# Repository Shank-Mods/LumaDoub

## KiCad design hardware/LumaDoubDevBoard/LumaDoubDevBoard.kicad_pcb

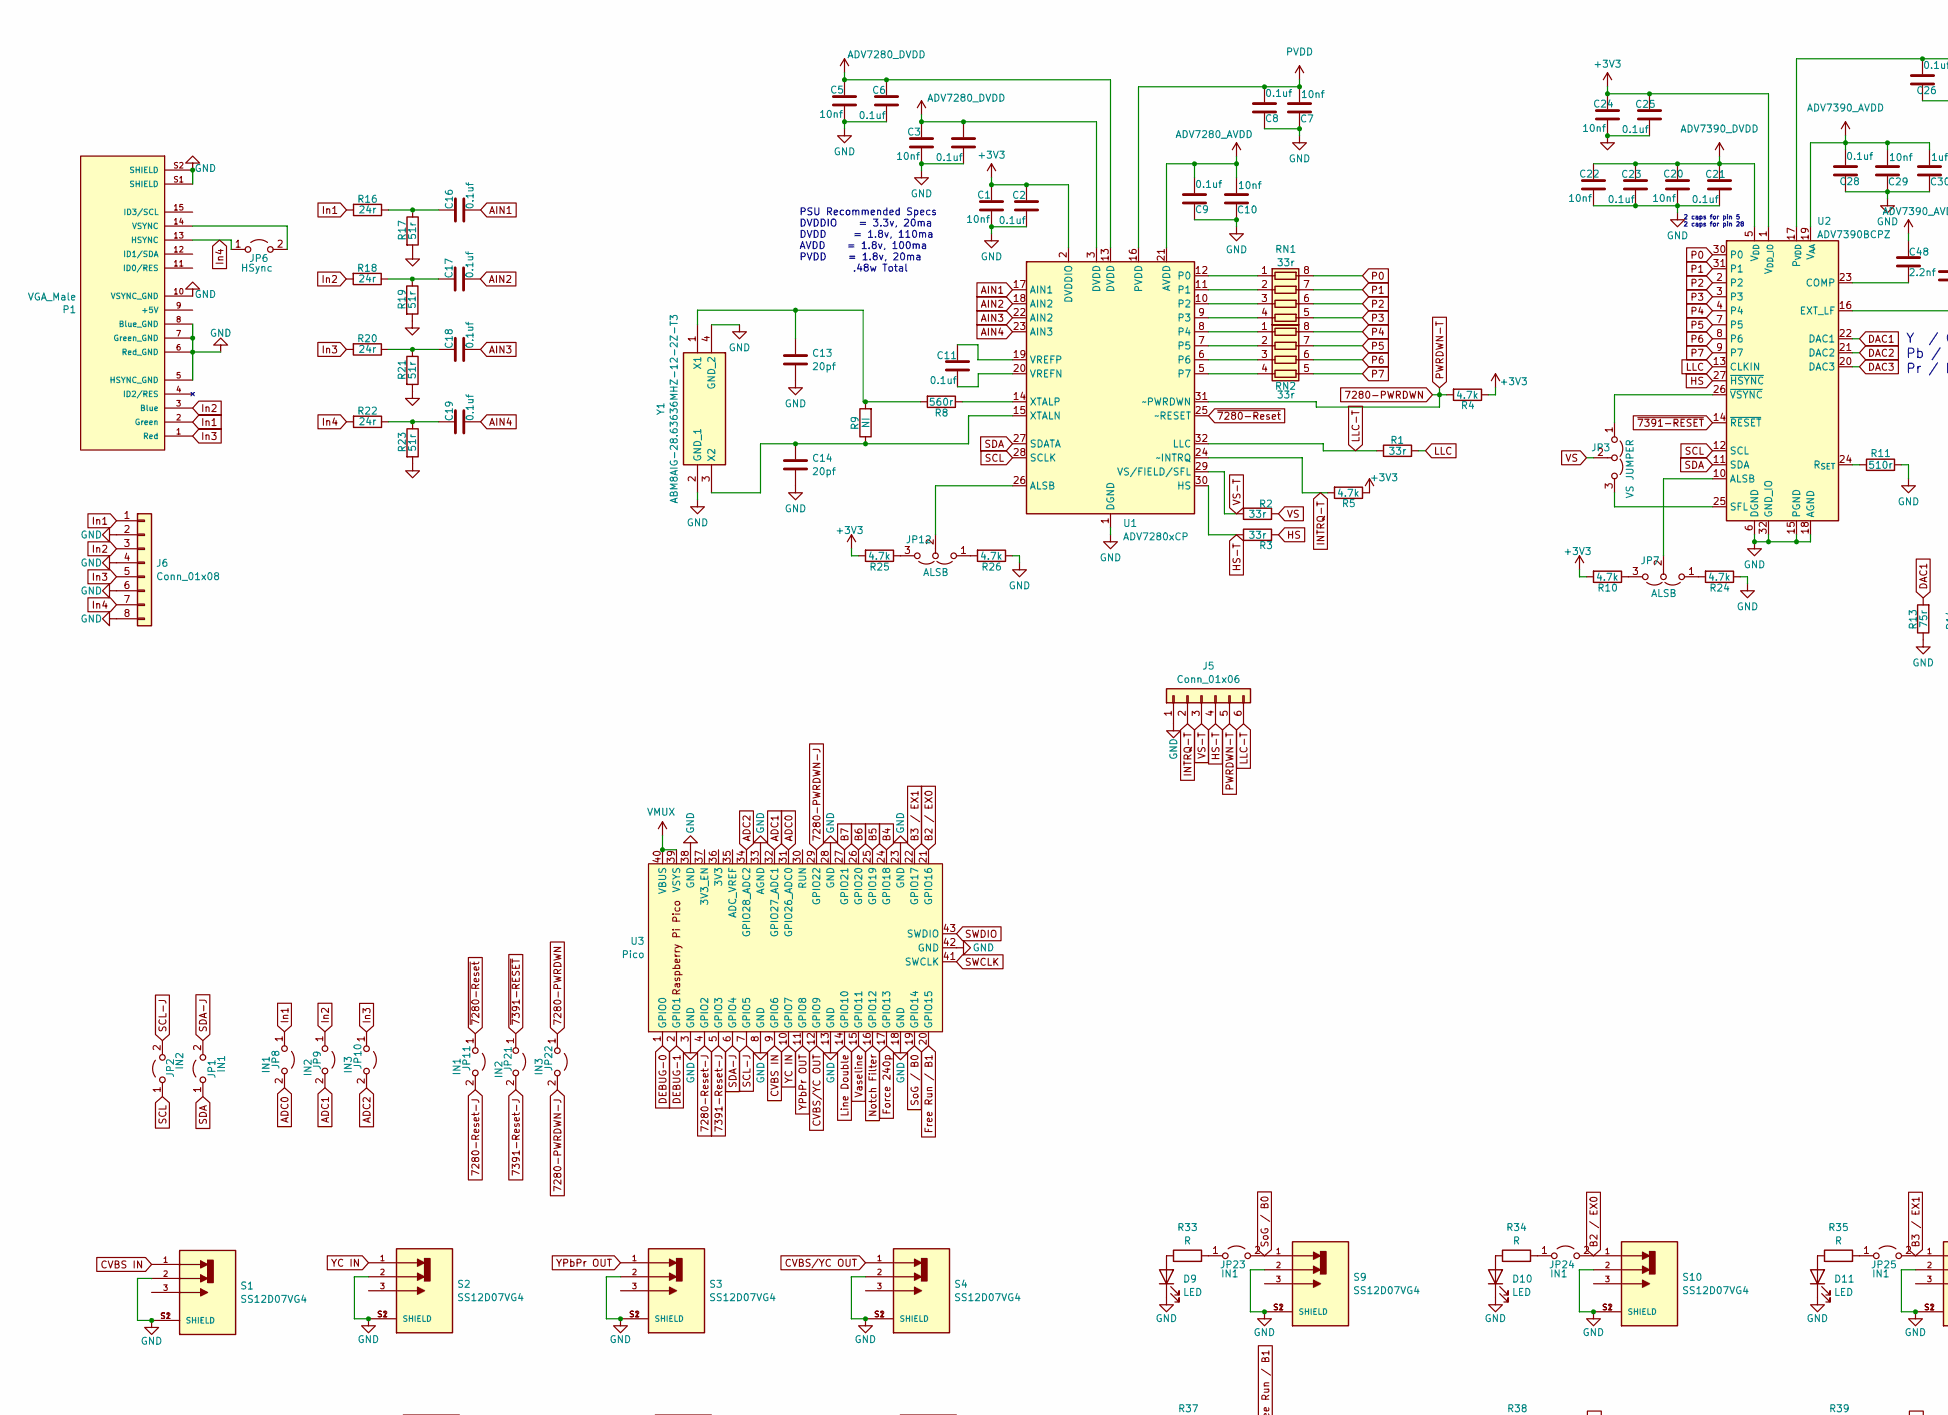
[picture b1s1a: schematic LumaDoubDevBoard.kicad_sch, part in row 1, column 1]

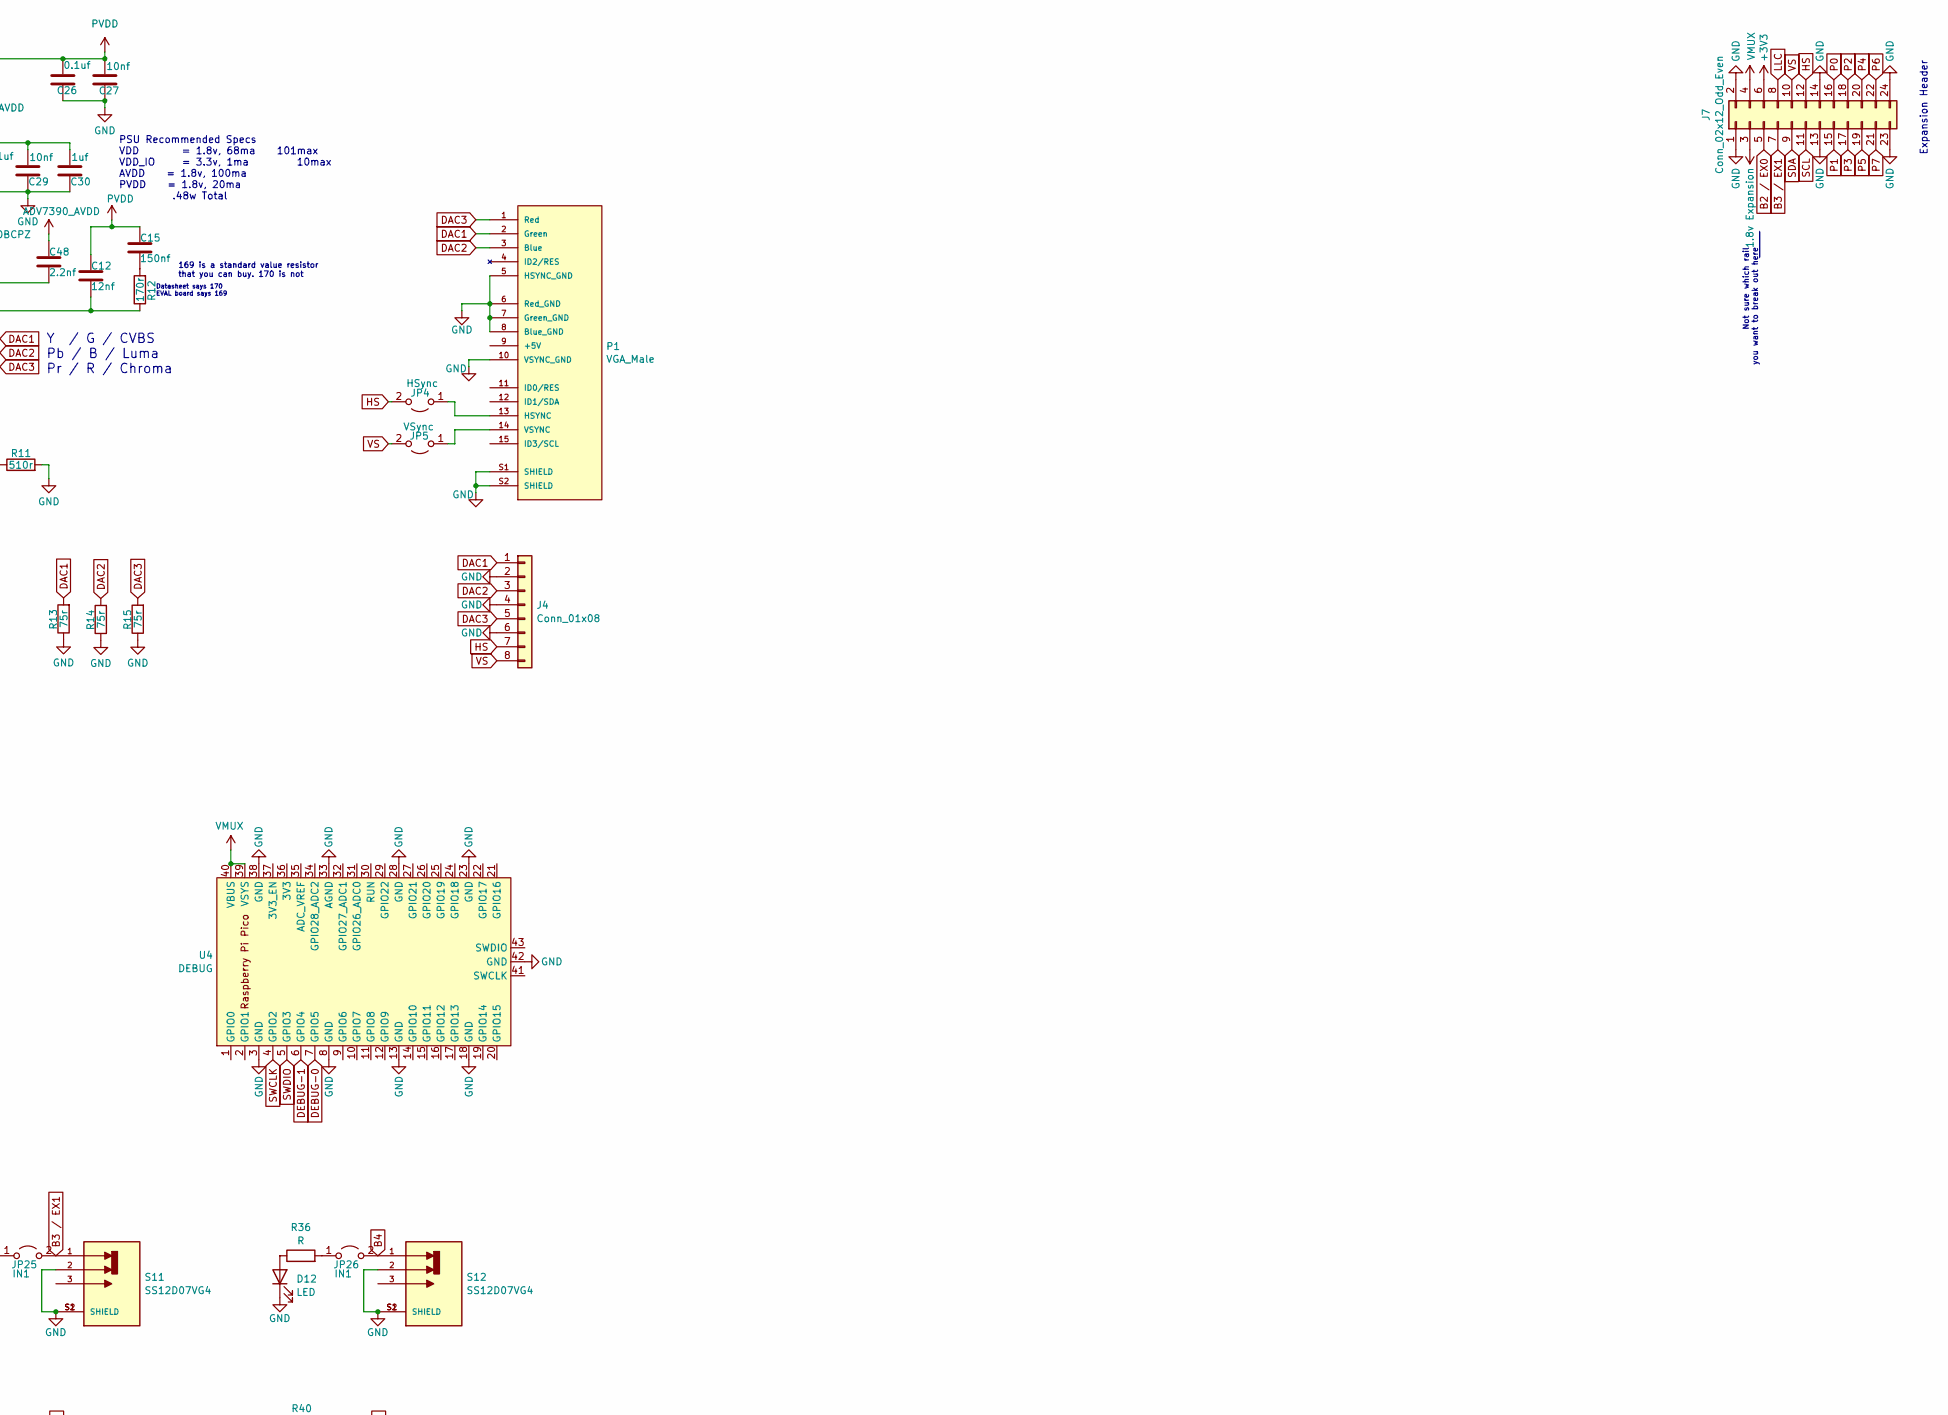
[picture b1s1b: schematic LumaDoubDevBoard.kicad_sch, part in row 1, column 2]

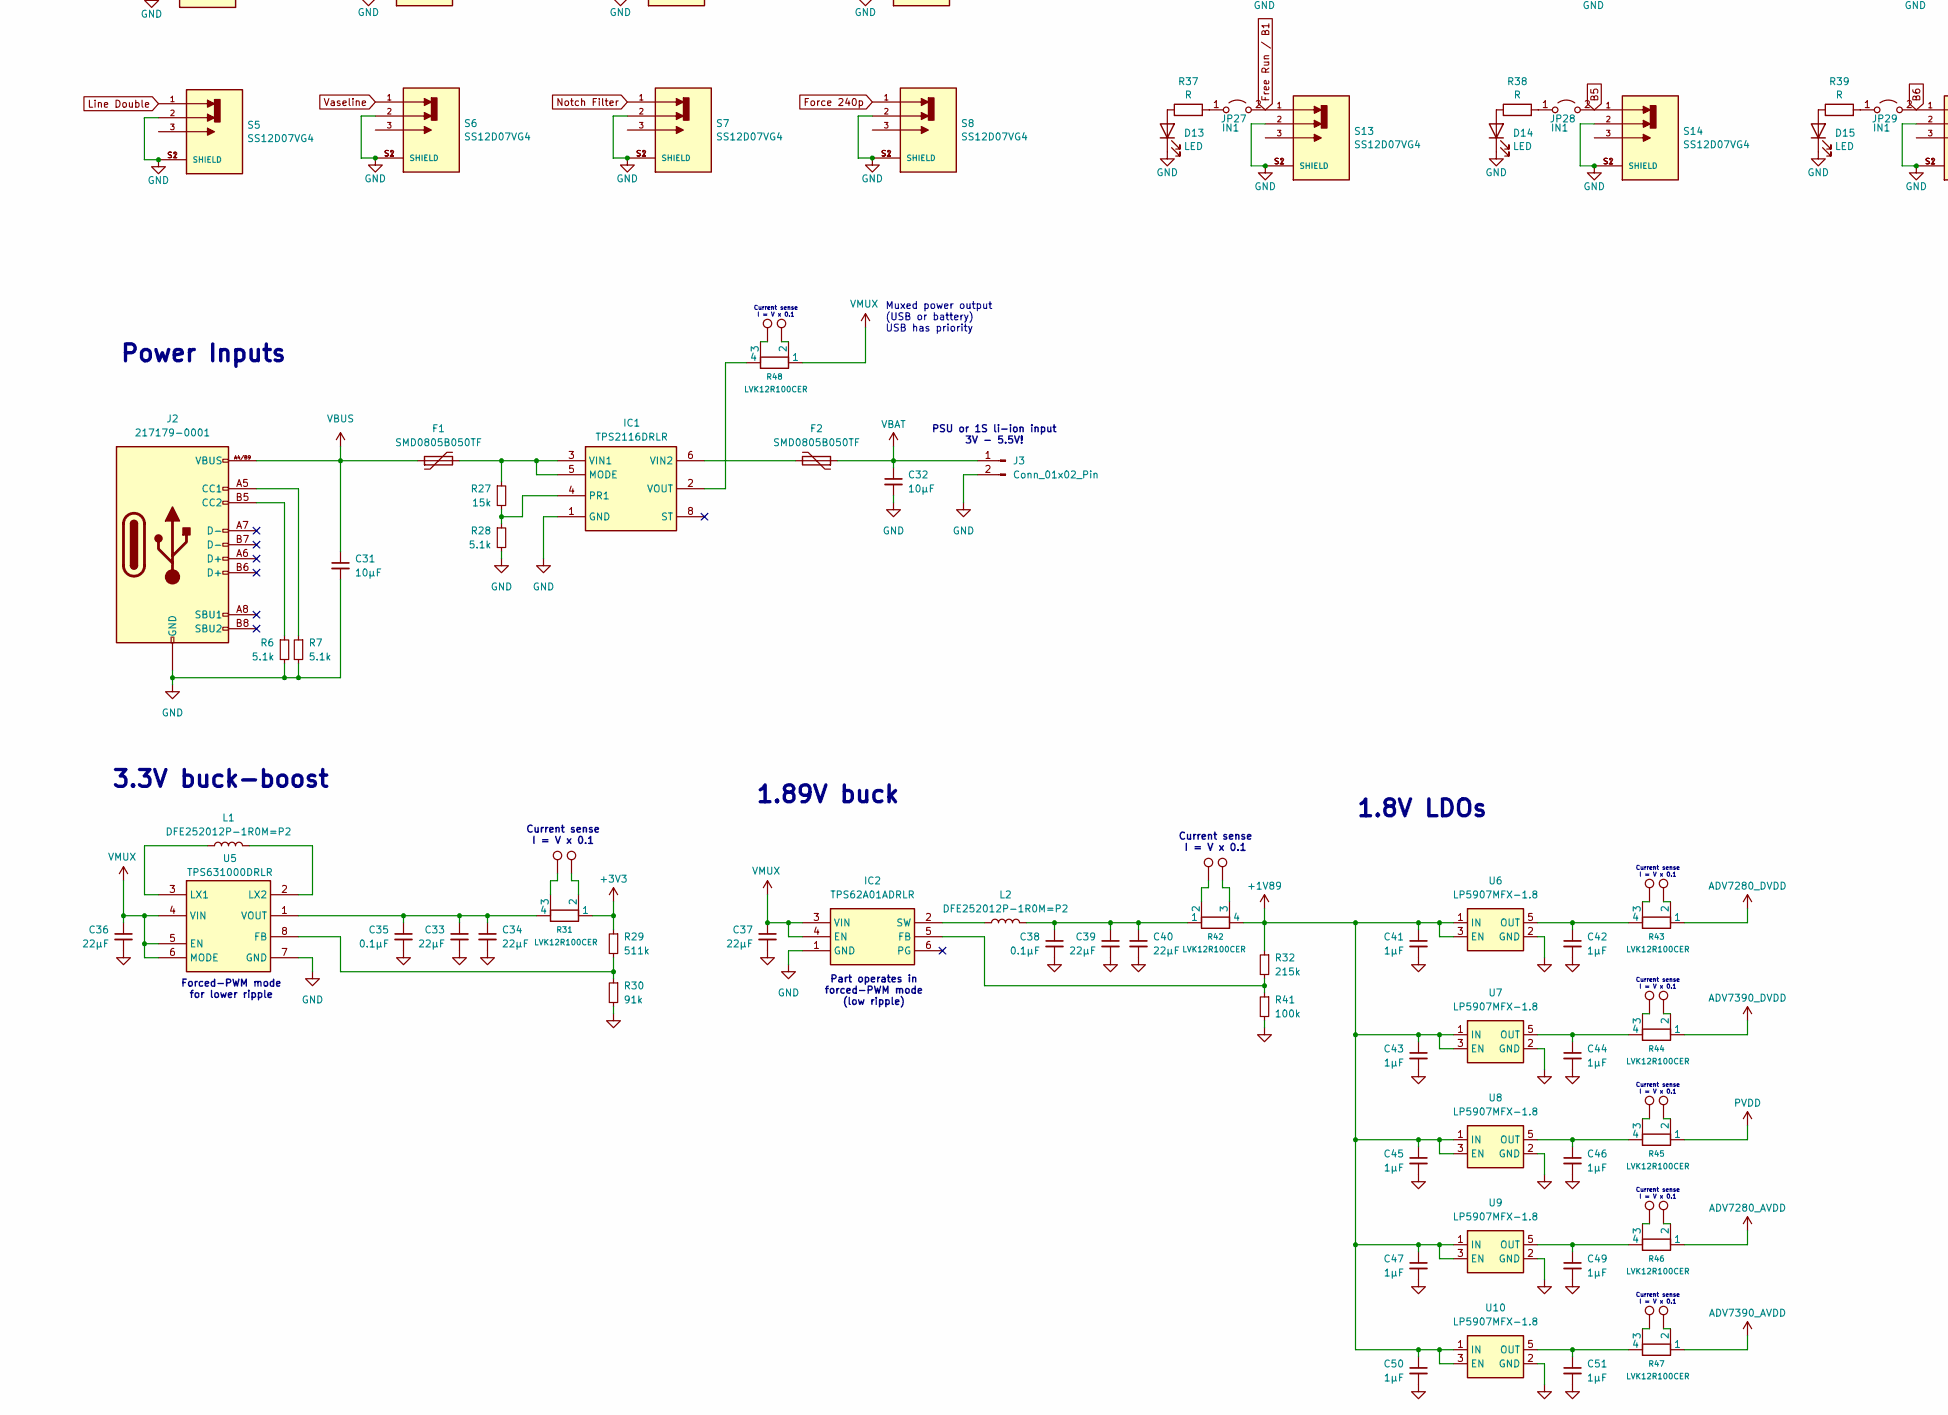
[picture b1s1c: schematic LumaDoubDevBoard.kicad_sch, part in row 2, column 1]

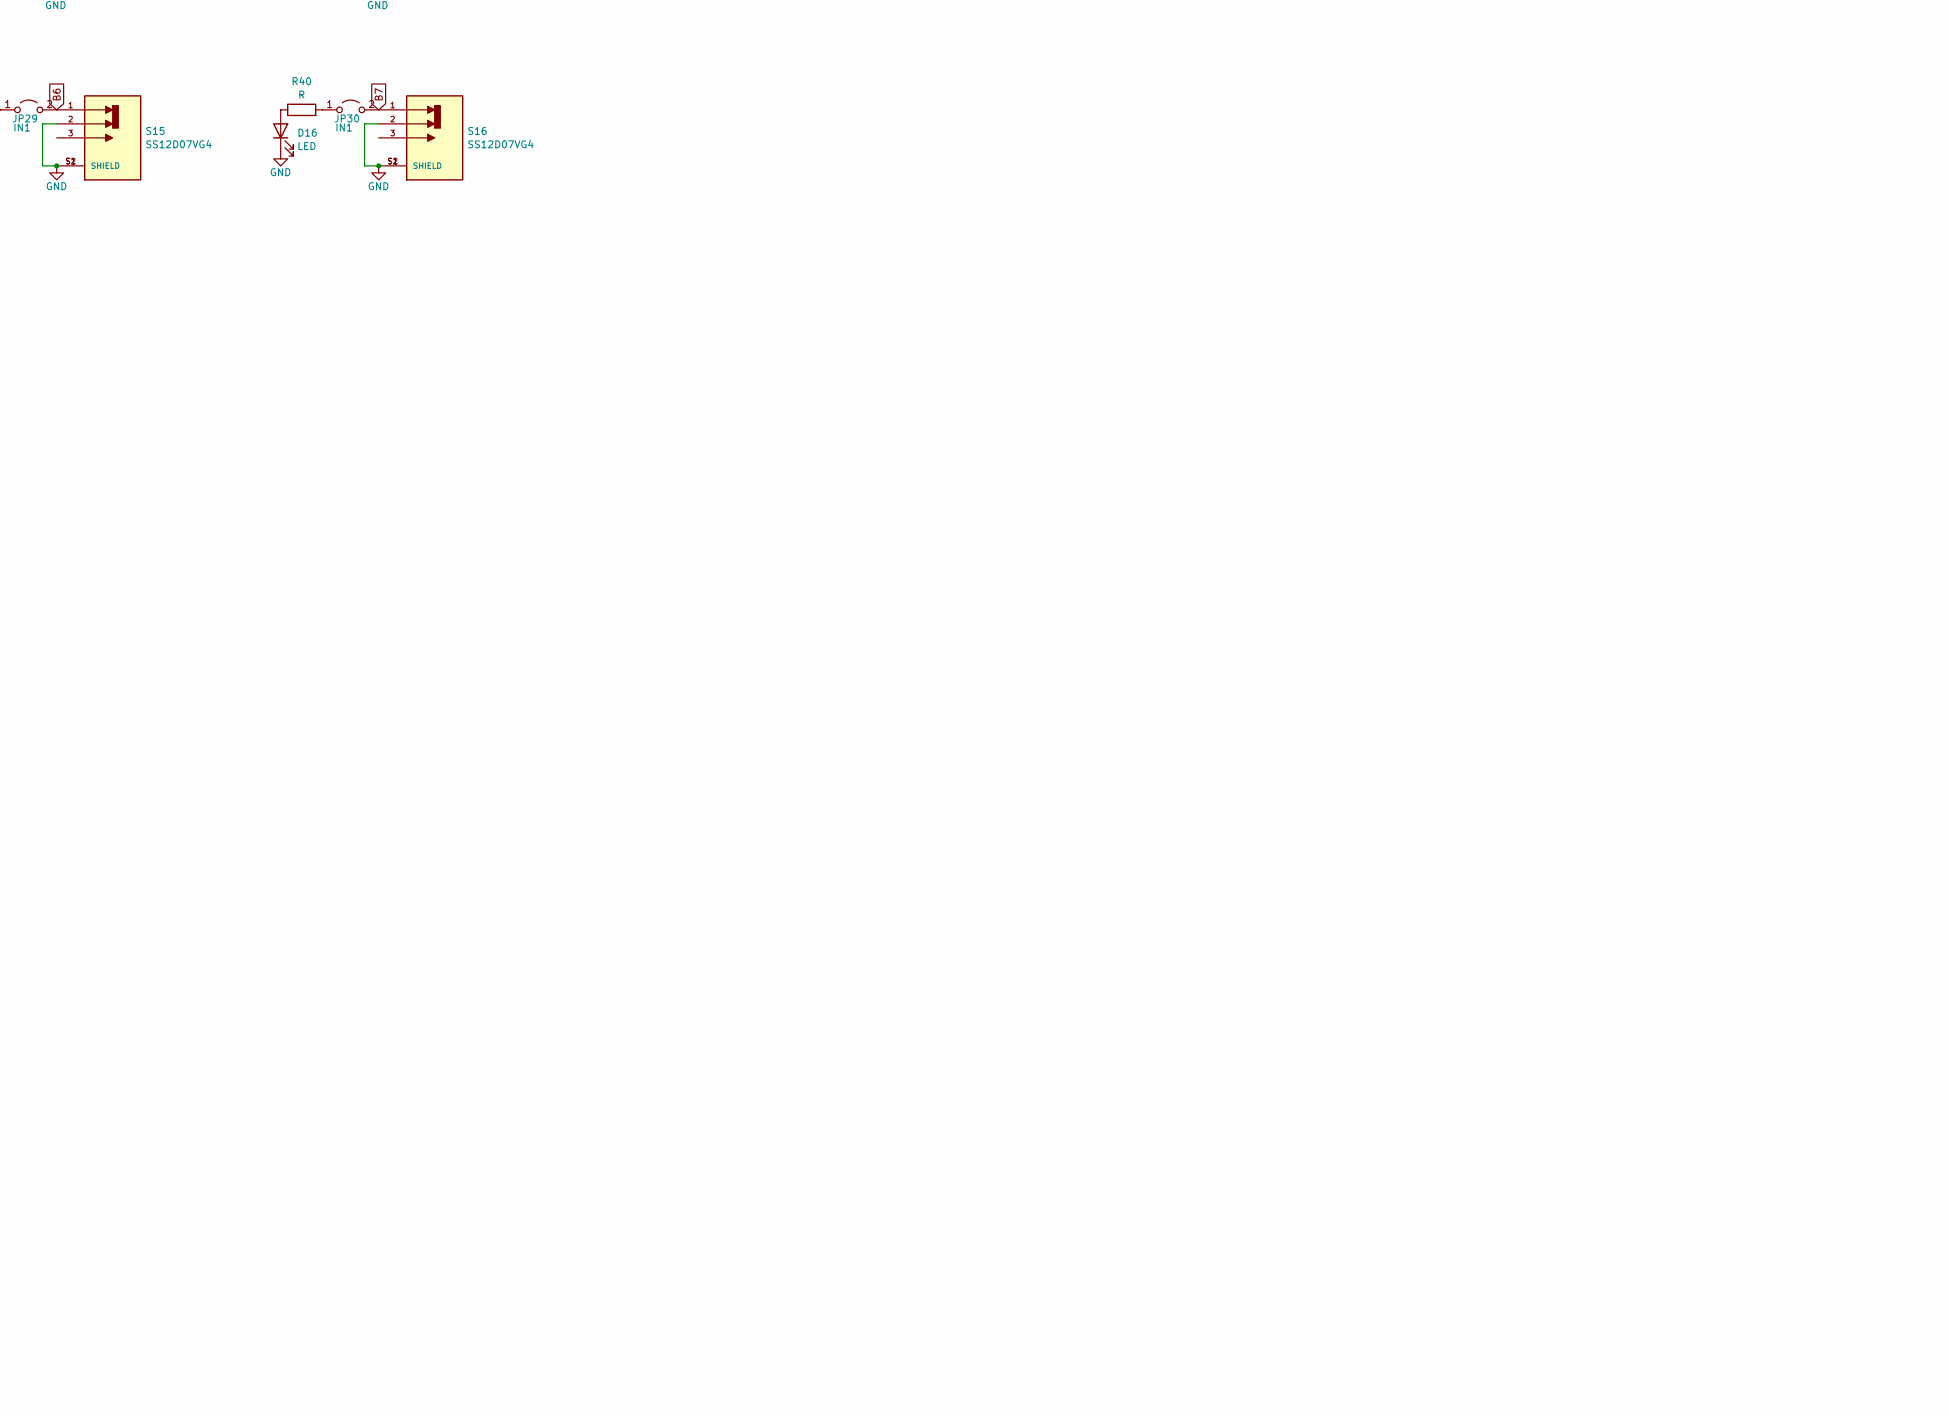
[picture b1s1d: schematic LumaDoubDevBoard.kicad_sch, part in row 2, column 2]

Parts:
C1, C3, C5, C7, C10, C20, C22, C24, C27, C29: 10nf; Cap_SMD_0603
C2, C4, C6, C8, C9, C11, C16, C17, C18, C19, C21, C23, C25, C26, C28: 0.1uf; Cap_SMD_0603
C12: 12nf; Cap_SMD_0603
C13, C14: 20pf; Cap_SMD_0603
C15: 150nf; Cap_SMD_0603
C30: 1uf; Cap_SMD_0603
C31, C32: 10μF; C_0603_1608Metric
C33, C34, C36, C37, C39, C40: 22μF; C_0603_1608Metric
C35, C38: 0.1μF; C_0402_1005Metric
C41, C42, C43, C44, C45, C46, C47, C49, C50, C51: 1μF; C_0402_1005Metric
C48: 2.2nf; Cap_SMD_0603
D9, D10, D11, D12, D13, D14, D15, D16: LED; LED_D5.0mm
F1, F2: SMD0805B050TF; Fuse_0805_2012Metric
IC1: TPS2116DRLR; SOTFL50P160X60-8N; Mouser Part Number 595-TPS2116DRLR
IC2: TPS62A01ADRLR; SOTFL50P160X60-6N; Mouser Part Number 595-TPS62A01ADRLR
J2: 217179-0001; 2171790001
J3: Conn_01x02_Pin; PinHeader_1x02_P2.54mm_Vertical
J4, J6: Conn_01x08; PinHeader_1x08_P2.54mm_Vertical
J5: Conn_01x06; PinHeader_1x06_P2.54mm_Vertical
J7: Conn_02x12_Odd_Even; PinHeader_2x12_P2.54mm_Vertical
JP1, JP8, JP11, JP23, JP24, JP25, JP26, JP27, JP28, JP29, JP30: IN1; SolderJumper-2_P1.3mm_Open_TrianglePad1.0x1.5mm
JP2, JP9, JP21: IN2; SolderJumper-2_P1.3mm_Open_TrianglePad1.0x1.5mm
JP3: VS JUMPER; SolderJumper-3_P2.0mm_Open_TrianglePad1.0x1.5mm
JP4, JP6: HSync; SolderJumper-2_P1.3mm_Open_TrianglePad1.0x1.5mm
JP5: VSync; SolderJumper-2_P1.3mm_Open_TrianglePad1.0x1.5mm
JP7, JP12: ALSB; SolderJumper-3_P2.0mm_Open_TrianglePad1.0x1.5mm
JP10, JP22: IN3; SolderJumper-2_P1.3mm_Open_TrianglePad1.0x1.5mm
L1, L2: DFE252012P-1R0M=P2; L_1008_2520Metric
P1: VGA_Male; VGA_male_rightangle_slim; PARTREV N/A
R1, R2, R3: 33r; R_0603_1608Metric
R4, R5, R10, R24, R25, R26: 4.7k; R_0603_1608Metric
R6, R7, R28: 5.1k; R_0402_1005Metric
R8: 560r; R_0603_1608Metric
R9: NI; R_0603_1608Metric
R11: 510r; R_0603_1608Metric
R12: 170r; R_0603_1608Metric
R13, R14, R15: 75r; R_0603_1608Metric
R16, R18, R20, R22: 24r; R_0603_1608Metric
R17, R19, R21, R23: 51r; R_0603_1608Metric
R27: 15k; R_0402_1005Metric
R29: 511k; R_0402_1005Metric
R30: 91k; R_0402_1005Metric
R31, R42, R43, R44, R45, R46, R47, R48: LVK12R100CER; R_Shunt_Ohmite_LVK12
R32: 215k; R_0402_1005Metric
R33, R34, R35, R36, R37, R38, R39, R40: R; R_0603_1608Metric
R41: 100k; R_0402_1005Metric
RN1, RN2: 33r; R_Array_Convex_4x1206
S1, S2, S3, S4, S5, S6, S7, S8, S9, S10, S11, S12, S13, S14, S15, S16: SS12D07VG4; SW_SS12D07VG4; PARTREV 1
TP13, TP14, TP15, TP16, TP17, TP18, TP19, TP20, TP21, TP22, TP23, TP24, TP25, TP26, TP27, TP28: TestPoint; TestPoint_THTPad_D1.5mm_Drill0.7mm
U1: ADV7280xCP; LFCSP-32-1EP_5x5mm_P0.5mm_EP3.6x3.6mm
U2: ADV7390BCPZ; LFCSP-32-1EP_5x5mm_P0.5mm_EP3.1x3.1mm
U3: Pico; RPi_Pico_SMD_TH
U4: DEBUG; RPi_Pico_SMD_TH
U5: TPS631000DRLR; SOTFL50P160X60-8N; Mouser Part Number 595-TPS631000DRLR
U6, U7, U8, U9, U10: LP5907MFX-1.8; SOT-23-5
Y1: ABM8AIG-28.63636MHZ-12-2Z-T3; ABM8AIG25000MHZ122ZT3; Mouser Part Number 815-MAIG28.6-12-2ZT3

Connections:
1.8v Expansion: J7.3
7280-PWRDWN: J5.5, JP22.1 (A), R4.2, U1.31 (~PWRDWN)
7280-PWRDWN-J: JP22.2 (B), U3.29 (GPIO22)
7280-Reset-J: JP11.2 (B), U3.4 (GPIO2)
7391-Reset-J: JP21.2 (B), U3.5 (GPIO3)
+1V89: C41.1, C43.1, C45.1, C47.1, C50.1, R32.1, R42.4, U6.1 (IN), U6.3 (EN), U7.1 (IN), U7.3 (EN), U8.1 (IN), U8.3 (EN), U9.1 (IN), U9.3 (EN), U10.1 (IN), U10.3 (EN)
+3V3: C1.1, C2.1, C24.1, C25.1, J7.6, R4.1, R5.1, R10.2, R25.2, R29.1, R31.1, U1.2 (DVDDIO), U2.1 (V_{DD_IO})
ADC0: JP8.2 (B), U3.31 (GPIO26_ADC0)
ADC1: JP9.2 (B), U3.32 (GPIO27_ADC1)
ADC2: JP10.2 (B), U3.34 (GPIO28_ADC2)
ADV7280_AVDD: C9.2, C10.2, R46.1, U1.21 (AVDD)
ADV7280_DVDD: C3.1, C4.1, C5.1, C6.1, R43.1, U1.3 (DVDD), U1.13 (DVDD)
ADV7390_AVDD: C28.2, C29.2, C30.2, C48.1, R47.1, U2.19 (V_{AA})
ADV7390_DVDD: C20.1, C21.1, C22.1, C23.1, R44.1, U2.5 (V_{DD}), U2.28 (V_{DD})
AIN1: C16.2, U1.17 (AIN1)
AIN2: C17.2, U1.18 (AIN2)
AIN3: C18.2, U1.22 (AIN2)
AIN4: C19.2, U1.23 (AIN3)
B2 / EX0: J7.5, JP24.2 (B), S10.1, U3.21 (GPIO16)
B3 / EX1: J7.7, JP25.2 (B), S11.1, U3.22 (GPIO17)
B4: JP26.2 (B), S12.1, U3.24 (GPIO18)
B5: JP28.2 (B), S14.1, U3.25 (GPIO19)
B6: JP29.2 (B), S15.1, U3.26 (GPIO20)
B7: JP30.2 (B), S16.1, U3.27 (GPIO21)
CVBS IN: S1.1, U3.9 (GPIO6)
CVBS/YC OUT: S4.1, U3.12 (GPIO9)
DEBUG-0: U3.1 (GPIO0), U4.7 (GPIO5)
DEBUG-1: U3.2 (GPIO1), U4.6 (GPIO4)
Force 240p: S8.1, U3.17 (GPIO13)
Free Run / B1: JP27.2 (B), S13.1, U3.20 (GPIO15)
GND: C1.2, C2.2, C3.2, C4.2, C5.2, C6.2, C7.1, C8.1, C9.1, C10.1, C13.1, C14.1, C20.2, C21.2, C22.2, C23.2, C24.2, C25.2, C26.1, C27.1, C28.1, C29.1, C30.1, C31.2, C32.2, C33.2, C34.2, C35.2, C36.2, C37.2, C38.2, C39.2, C40.2, C41.2, C42.2, C43.2, C44.2, C45.2, C46.2, C47.2, C49.2, C50.2, C51.2, D9.1 (K), D10.1 (K), D11.1 (K), D12.1 (K), D13.1 (K), D14.1 (K), D15.1 (K), D16.1 (K), IC1.1 (GND), IC2.1 (GND), J2.1 (GND), J2.2 (GND), J2.3 (GND), J2.4 (GND), J2.13 (GND), J2.14 (GND), J2.15 (GND), J2.16 (GND), J2.A1/B12 (GND_2), J2.B1/A12 (GND), J2.S_1_H1 (GND), J2.S_1_H2 (GND), J2.S_2_H1 (GND), J2.S_2_H2 (GND), J2.S_3_H1 (GND), J2.S_3_H2 (GND), J2.S_4_H1 (GND), J2.S_4_H2 (GND), J3.2, J4.2, J4.4, J4.6, J5.1, J6.2, J6.4, J6.6, J6.8, J7.1, J7.2, J7.13, J7.14, J7.23, J7.24, P1.5 (HSYNC_GND), P1.6 (Red_GND), P1.7 (Green_GND), P1.8 (Blue_GND), P1.10 (VSYNC_GND), P1.S1 (SHIELD), P1.S2 (SHIELD), R6.2, R7.2, R11.2, R13.1, R14.1, R15.1, R17.2, R19.2, R21.2, R23.2, R24.1, R26.1, R28.2, R30.2, R41.2, S1.2, S1.S1 (SHIELD), S1.S2 (SHIELD), S2.2, S2.S1 (SHIELD), S2.S2 (SHIELD), S3.2, S3.S1 (SHIELD), S3.S2 (SHIELD), S4.2, S4.S1 (SHIELD), S4.S2 (SHIELD), S5.2, S5.S1 (SHIELD), S5.S2 (SHIELD), S6.2, S6.S1 (SHIELD), S6.S2 (SHIELD), S7.2, S7.S1 (SHIELD), S7.S2 (SHIELD), S8.2, S8.S1 (SHIELD), S8.S2 (SHIELD), S9.2, S9.S1 (SHIELD), S9.S2 (SHIELD), S10.2, S10.S1 (SHIELD), S10.S2 (SHIELD), S11.2, S11.S1 (SHIELD), S11.S2 (SHIELD), S12.2, S12.S1 (SHIELD), S12.S2 (SHIELD), S13.2, S13.S1 (SHIELD), S13.S2 (SHIELD), S14.2, S14.S1 (SHIELD), S14.S2 (SHIELD), S15.2, S15.S1 (SHIELD), S15.S2 (SHIELD), S16.2, S16.S1 (SHIELD), S16.S2 (SHIELD), U1.1 (DGND), U1.4 (DGND), U1.33 (DGND), U2.6 (DGND), U2.15 (PGND), U2.18 (AGND), U2.29 (DGND), U2.32 (GND_IO), U2.33 (AGND), U3.3 (GND), U3.8 (GND), U3.13 (GND), U3.18 (GND), U3.23 (GND), U3.28 (GND), U3.33 (AGND), U3.38 (GND), U3.42 (GND), U4.3 (GND), U4.8 (GND), U4.13 (GND), U4.18 (GND), U4.23 (GND), U4.28 (GND), U4.33 (AGND), U4.38 (GND), U4.42 (GND), U5.7 (GND), U6.2 (GND), U7.2 (GND), U8.2 (GND), U9.2 (GND), U10.2 (GND), Y1.2 (GND_1), Y1.4 (GND_2); also elsewhere on the board
HS: J4.7, J7.12, JP4.2 (B), R3.2, U2.27 (~HSYNC)
HS-T: J5.4, R3.1, U1.30 (HS)
INTRQ-T: J5.2, R5.2, U1.24 (~INTRQ)
LLC: J7.8, R1.2, U2.13 (CLKIN)
LLC-T: J5.6, R1.1, U1.32 (LLC)
Line Double: S5.1, U3.14 (GPIO10)
unnamed: C15.2, R12.2
unnamed: C16.1, R16.1, R17.1
unnamed: C17.1, R18.1, R19.1
unnamed: C18.1, R20.1, R21.1
unnamed: C19.1, R22.1, R23.1
unnamed: C38.1, C39.1, C40.1, L2.2, R42.1
unnamed: D9.2 (A), R33.1
unnamed: D10.2 (A), R34.1
unnamed: D11.2 (A), R35.1
unnamed: D12.2 (A), R36.1
unnamed: D13.2 (A), R37.1
unnamed: D14.2 (A), R38.1
unnamed: D15.2 (A), R39.1
unnamed: D16.2 (A), R40.1
unnamed: F1.2, IC1.3 (VIN1), IC1.5 (MODE), R27.1
unnamed: IC1.4 (PR1), R27.2, R28.1
unnamed: F2.2, IC1.6 (VIN2)
unnamed: IC1.2 (VOUT), IC1.7 (VOUT_2), R48.4
unnamed: IC2.5 (FB), R32.2, R41.1
unnamed: IC2.2 (SW), L2.1
unnamed: J2.A5 (CC1), R7.1
unnamed: J2.B5 (CC2), R6.1
unnamed: JP3.1 (A), U2.26 (~VSYNC)
unnamed: JP3.3 (B), U2.25 (SFL)
unnamed: JP7.1 (A), R24.2
unnamed: JP7.3 (B), R10.1
unnamed: JP7.2 (C), U2.10 (ALSB)
unnamed: JP12.1 (A), R26.2
unnamed: JP12.3 (B), R25.1
unnamed: JP12.2 (C), U1.26 (ALSB)
unnamed: JP23.1 (A), R33.2
unnamed: JP24.1 (A), R34.2
unnamed: JP25.1 (A), R35.2
unnamed: JP26.1 (A), R36.2
unnamed: JP27.1 (A), R37.2
unnamed: JP28.1 (A), R38.2
unnamed: JP29.1 (A), R39.2
unnamed: JP30.1 (A), R40.2
unnamed: R31.2, TP14.1
unnamed: R31.3, TP13.1
unnamed: R42.2, TP15.1
unnamed: R42.3, TP16.1
unnamed: R43.2, TP18.1
unnamed: R43.3, TP17.1
unnamed: R44.2, TP20.1
unnamed: R44.3, TP19.1
unnamed: R45.2, TP22.1
unnamed: R45.3, TP21.1
unnamed: R46.2, TP24.1
unnamed: R46.3, TP23.1
unnamed: R47.2, TP26.1
unnamed: R47.3, TP25.1
unnamed: R48.2, TP28.1
unnamed: R48.3, TP27.1
unnamed: RN1.1 (R1.1), U1.12 (P0)
unnamed: RN1.2 (R2.1), U1.11 (P1)
unnamed: RN1.3 (R3.1), U1.10 (P2)
unnamed: RN1.4 (R4.1), U1.9 (P3)
unnamed: RN2.1 (R1.1), U1.8 (P4)
unnamed: RN2.2 (R2.1), U1.7 (P5)
unnamed: RN2.3 (R3.1), U1.6
unnamed: RN2.4 (R4.1), U1.5 (P7)
unnamed: C11.2, U1.20 (VREFN)
unnamed: C11.1, U1.19 (VREFP)
unnamed: C14.2, R9.1, U1.15 (XTALN), Y1.3 (X2)
unnamed: R8.1, U1.14 (XTALP)
unnamed: C48.2, U2.23 (COMP)
unnamed: C12.2, R12.1, U2.16 (EXT_LF)
unnamed: R11.1, U2.24 (R_{SET})
unnamed: R29.2, R30.1, U5.8 (FB)
unnamed: L1.1, U5.3 (LX1)
unnamed: L1.2, U5.2 (LX2)
unnamed: C33.1, C34.1, C35.1, R31.4, U5.1 (VOUT)
unnamed: C42.1, R43.4, U6.5 (OUT)
unnamed: C44.1, R44.4, U7.5 (OUT)
unnamed: C46.1, R45.4, U8.5 (OUT)
unnamed: C49.1, R46.4, U9.5 (OUT)
unnamed: C51.1, R47.4, U10.5 (OUT)
unnamed: C13.2, R8.2, R9.2, Y1.1 (X1)
Notch Filter: S7.1, U3.16 (GPIO12)
P0: J7.16, RN1.8 (R1.2), U2.30 (P0)
P1: J7.15, RN1.7 (R2.2), U2.31 (P1)
P2: J7.18, RN1.6 (R3.2), U2.2
P3: J7.17, RN1.5 (R4.2), U2.3
P4: J7.20, RN2.8 (R1.2), U2.4
P5: J7.19, RN2.7 (R2.2), U2.7 (P5)
P6: J7.22, RN2.6 (R3.2), U2.8 (P6)
P7: J7.21, RN2.5 (R4.2), U2.9 (P7)
PVDD: C7.2, C8.2, C12.1, C15.1, C26.2, C27.2, R45.1, U1.16 (PVDD), U2.17 (P_{VDD})
SCL: J7.11, JP2.1 (A), U1.28 (SCLK), U2.12 (SCL)
SCL-J: JP2.2 (B), U3.7 (GPIO5)
SDA: J7.9, JP1.1 (A), U1.27 (SDATA), U2.11 (SDA)
SDA-J: JP1.2 (B), U3.6 (GPIO4)
SWCLK: U3.41 (SWCLK), U4.4 (GPIO2)
SWDIO: U3.43 (SWDIO), U4.5 (GPIO3)
SoG / B0: JP23.2 (B), S9.1, U3.19 (GPIO14)
VBAT: C32.1, F2.1, J3.1
VBUS: C31.1, F1.1, J2.A4/B9 (VBUS), J2.B4/A9 (VBUS)
VMUX: C36.1, C37.1, IC2.3 (VIN), IC2.4 (EN), J7.4, R48.1, U3.39 (VSYS), U3.40 (VBUS), U4.39 (VSYS), U4.40 (VBUS), U5.4 (VIN), U5.5 (EN), U5.6 (MODE)
VS: J4.8, J7.10, JP3.2 (C), JP5.2 (B), R2.2
VS-T: J5.3, R2.1, U1.29 (VS/FIELD/SFL)
Vaseline: S6.1, U3.15 (GPIO11)
YC IN: S2.1, U3.10 (GPIO7)
YPbPr OUT: S3.1, U3.11 (GPIO8)
~7280-Reset: JP11.1 (A), U1.25 (~RESET)
~7391-RESET: JP21.1 (A), U2.14 (~RESET)

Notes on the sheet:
Not sure which rail you want to break out here
Current sense I = V x 0.1
1.8V LDOs
Y / G / CVBS Pb / B / Luma Pr / R / Chroma
PSU Recommended Specs DVDDIO = 3.3v, 20ma DVDD = 1.8v, 110ma AVDD = 1.8v, 100ma PVDD = 1.8v, 20ma .48w Total
Forced-PWM mode for lower ripple
PSU Recommended Specs VDD = 1.8v, 68ma 101max VDD_IO = 3.3v, 1ma 10max AVDD = 1.8v, 100ma PVDD = 1.8v, 20ma .48w Total
Power Inputs
Part operates in forced-PWM mode (low ripple)
2 caps for pin 5 2 caps for pin 28
Expansion Header
Muxed power output (USB or battery) USB has priority
PSU or 1S li-ion input 3V - 5.5V!
169 is a standard value resistor that you can buy. 170 is not
1.89V buck
Datasheet says 170 EVAL board says 169
3.3V buck-boost

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
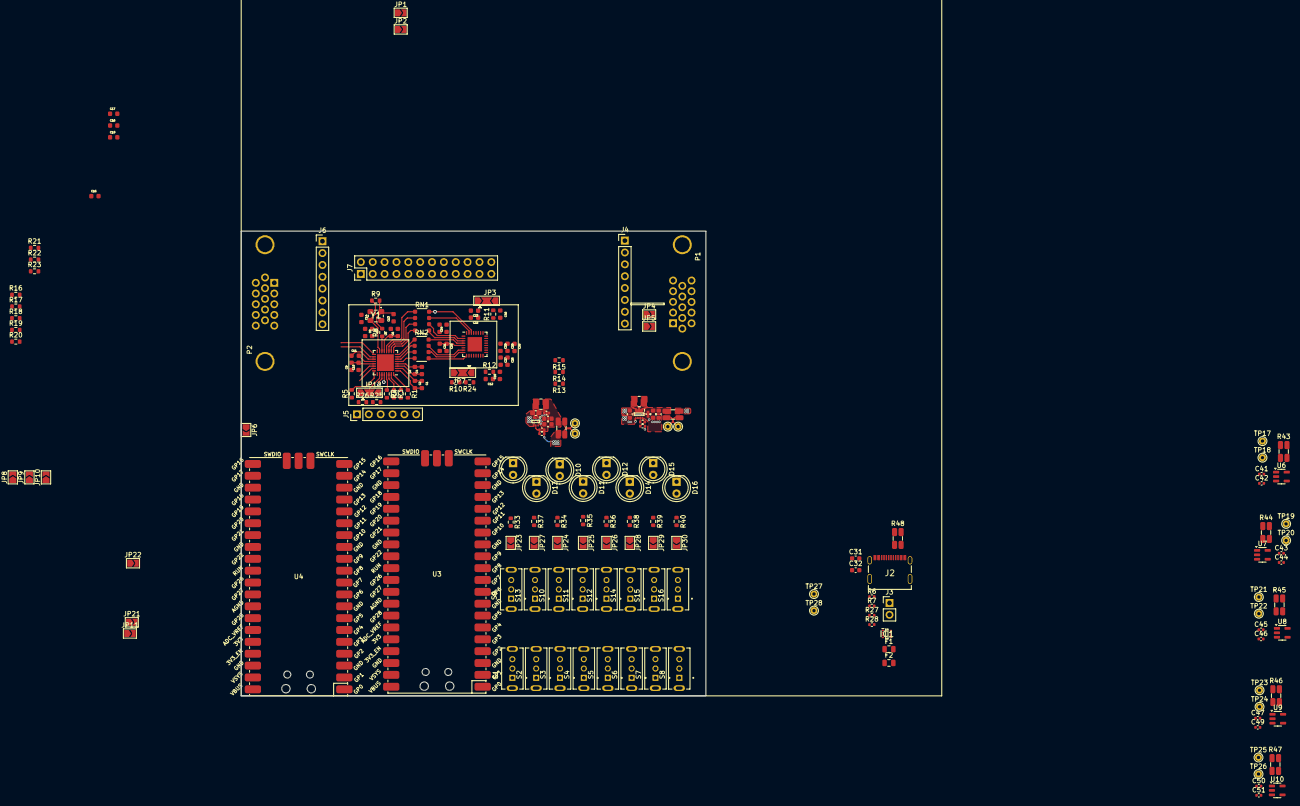
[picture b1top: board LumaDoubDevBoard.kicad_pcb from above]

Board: 4 copper layers, 99.5 x 99.5 mm, 188 parts (0 on the bottom side), 152 nets.

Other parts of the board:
P2: VGA_Male; VGA_male_rightangle_slim

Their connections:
GND: P2.5 (HSYNC_GND), P2.6 (Red_GND), P2.7 (Green_GND), P2.8 (Blue_GND), P2.10 (VSYNC_GND), P2.S1 (SHIELD), P2.S2 (SHIELD); also elsewhere on the board

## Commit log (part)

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2024-09-09 Add software directory
2024-09-10 Rename 'software' directory to 'firmware'
2024-09-10 Scaffold basic Pi Pico I2C project in firmware directory
2024-09-10 Add .clang-format
2024-09-10 Write first draft of basic I2C logic
    - Define type for I2C commands
    - Create functions to write commands to devices over I2C
    - From provided template scripts (https://www.analog.com/media/en/engineering-tools/design-tools/ADV7280A_Cust.zip), add I2C commands to configure ADV7280A and ADV7391
2024-09-12 Start Kicad dev board
2024-09-12 Saved the schematic
2024-09-12 Added to the Schematic, Started PCB Layout
2024-09-12 Add power management to schematic
2024-09-12 Update 3.3v buck-boost to FPWM mode
2024-09-12 Add current-sense to VMUX
2024-09-12 Restore WIP layout file
2024-09-13 Begun core component layout
2024-09-13 PCB layout progress
2024-09-14 PCB Work
2024-09-14 fix kicad files for 8.99.0.2194
2024-09-14 buck converter routing
2025-02-13 Pull reset lines for both chips low; disable first command in test script; write I2C with a timeout
    This version works.
2025-02-13 Create main polling loop; get some of the switches working in that loop
2025-02-15 Add "vaseline" (antialiasing filter) and line doubling switches
    Note: vaseline filter doesn't seem to be working yet.
2025-02-15 Add notes on some commands
2025-02-17 Enable flipping register bits using on-board switches; enable debug output over serial
2025-02-17 Add I2C read capability; force 240p when input signal is interlaced
2025-02-17 Implemented basic auto-input detection
2025-02-17 Route CVBS and YC through different inputs
2025-02-22 Autocycle between inputs; add vaseline and notch filters
    Includes a little bit of main loop tidying.
2025-02-27 Factor out init commands into separate function; remove unused device commands for CVBS in various inputs
2025-02-27 Fix autocycling issue: set next_input before entering the loop
    This fixes the case where the device starts in autocycle mode and never tries the next input, since next_input is null until the first valid signal is found
2025-02-27 Read and print value of VPP map register 0x5A
2025-02-27 Set custom register switches to toggle VPP map register 0x5A
2025-04-01 Many, many changes
2025-05-10 Autocycle fixes, test pattern switch fixing, register test reading
